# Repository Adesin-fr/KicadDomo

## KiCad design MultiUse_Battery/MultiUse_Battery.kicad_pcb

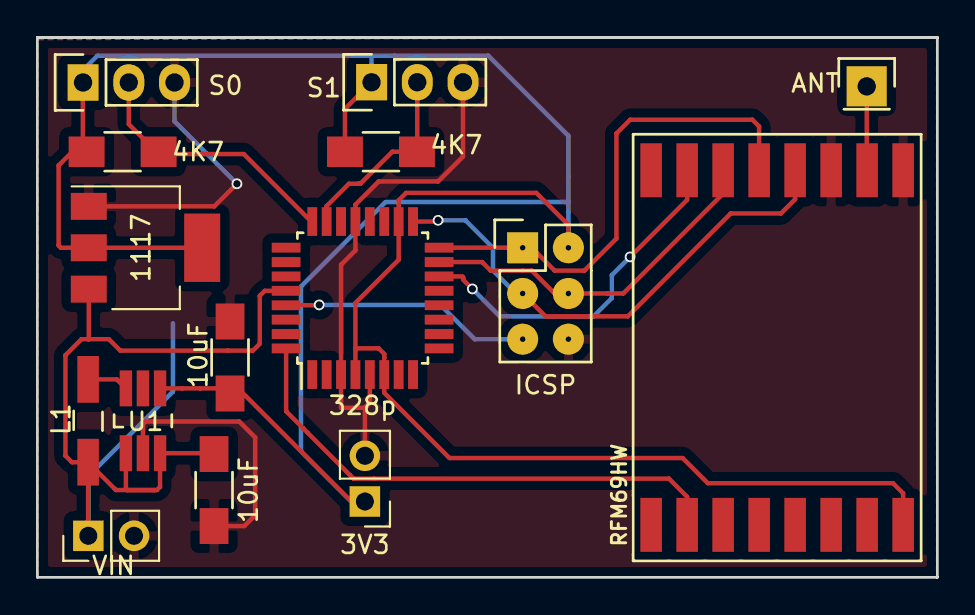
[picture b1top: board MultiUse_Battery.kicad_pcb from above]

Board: 2 copper layers, 50.0 x 30.0 mm, 16 parts (1 on the bottom side), 13 nets.

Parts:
3V3: CONN_01X02; Pin_Header_Straight_1x02_Pitch2.54mm
3V3#2: CR2032; BU2032_smd
4K7, 4K7#2: 4K7; R_1206_HandSoldering
10uF, 10uF#2: C; C_1206_HandSoldering
328p: ATMEGA328P-AU; TQFP-32_7x7mm_Pitch0.8mm
1117: AP111733; SOT-223
ANT: CONN_01X01; Pin_Header_Straight_1x01
ICSP: CONN_02X03; Pin_Header_Straight_2x03
L1: L; Choke_SMD_1206_Handsoldering
RFM69HW: RFM69HW; RFM69HW_SMD_Handsoldering
S0, S1: CONN_01X03; Pin_Header_Straight_1x03
U1: MAX1724; TSOT-6-MK06A_Handsoldering
VIN: CONN_01X02; Pin_Header_Straight_1x02_Pitch2.54mm

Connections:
/3V3: 3V3.1, 4K7.1, 4K7#2.1, 10uF#2.1, 328p.4, 328p.6, 328p.18, 1117.2, 1117.4, ICSP.2, RFM69HW.8, S0.1, S1.1, U1.4
/CSN: 328p.14, RFM69HW.15
/GND: 3V3.2, 3V3#2.2, 10uF.2, 10uF#2.2, 328p.3, 328p.5, 328p.21, 1117.1, ICSP.6, RFM69HW.9, RFM69HW.11, S0.3, S1.3, U1.2, VIN.2
/IRQ: 328p.32, RFM69HW.2
/MISO: 328p.16, ICSP.1, RFM69HW.13
/MOSI: 328p.15, ICSP.4, RFM69HW.14
/PC0: 4K7.2, 328p.24, S0.2
/PC1: 4K7#2.2, 328p.23, S1.2
/RST: 328p.29, ICSP.5
/SCK: 328p.17, ICSP.3, RFM69HW.12
/VIN: 3V3#2.1, 10uF.1, 328p.28, 1117.3, L1.1, U1.1, U1.3, VIN.1
unnamed: L1.2, U1.6
unnamed: ANT.1, RFM69HW.10

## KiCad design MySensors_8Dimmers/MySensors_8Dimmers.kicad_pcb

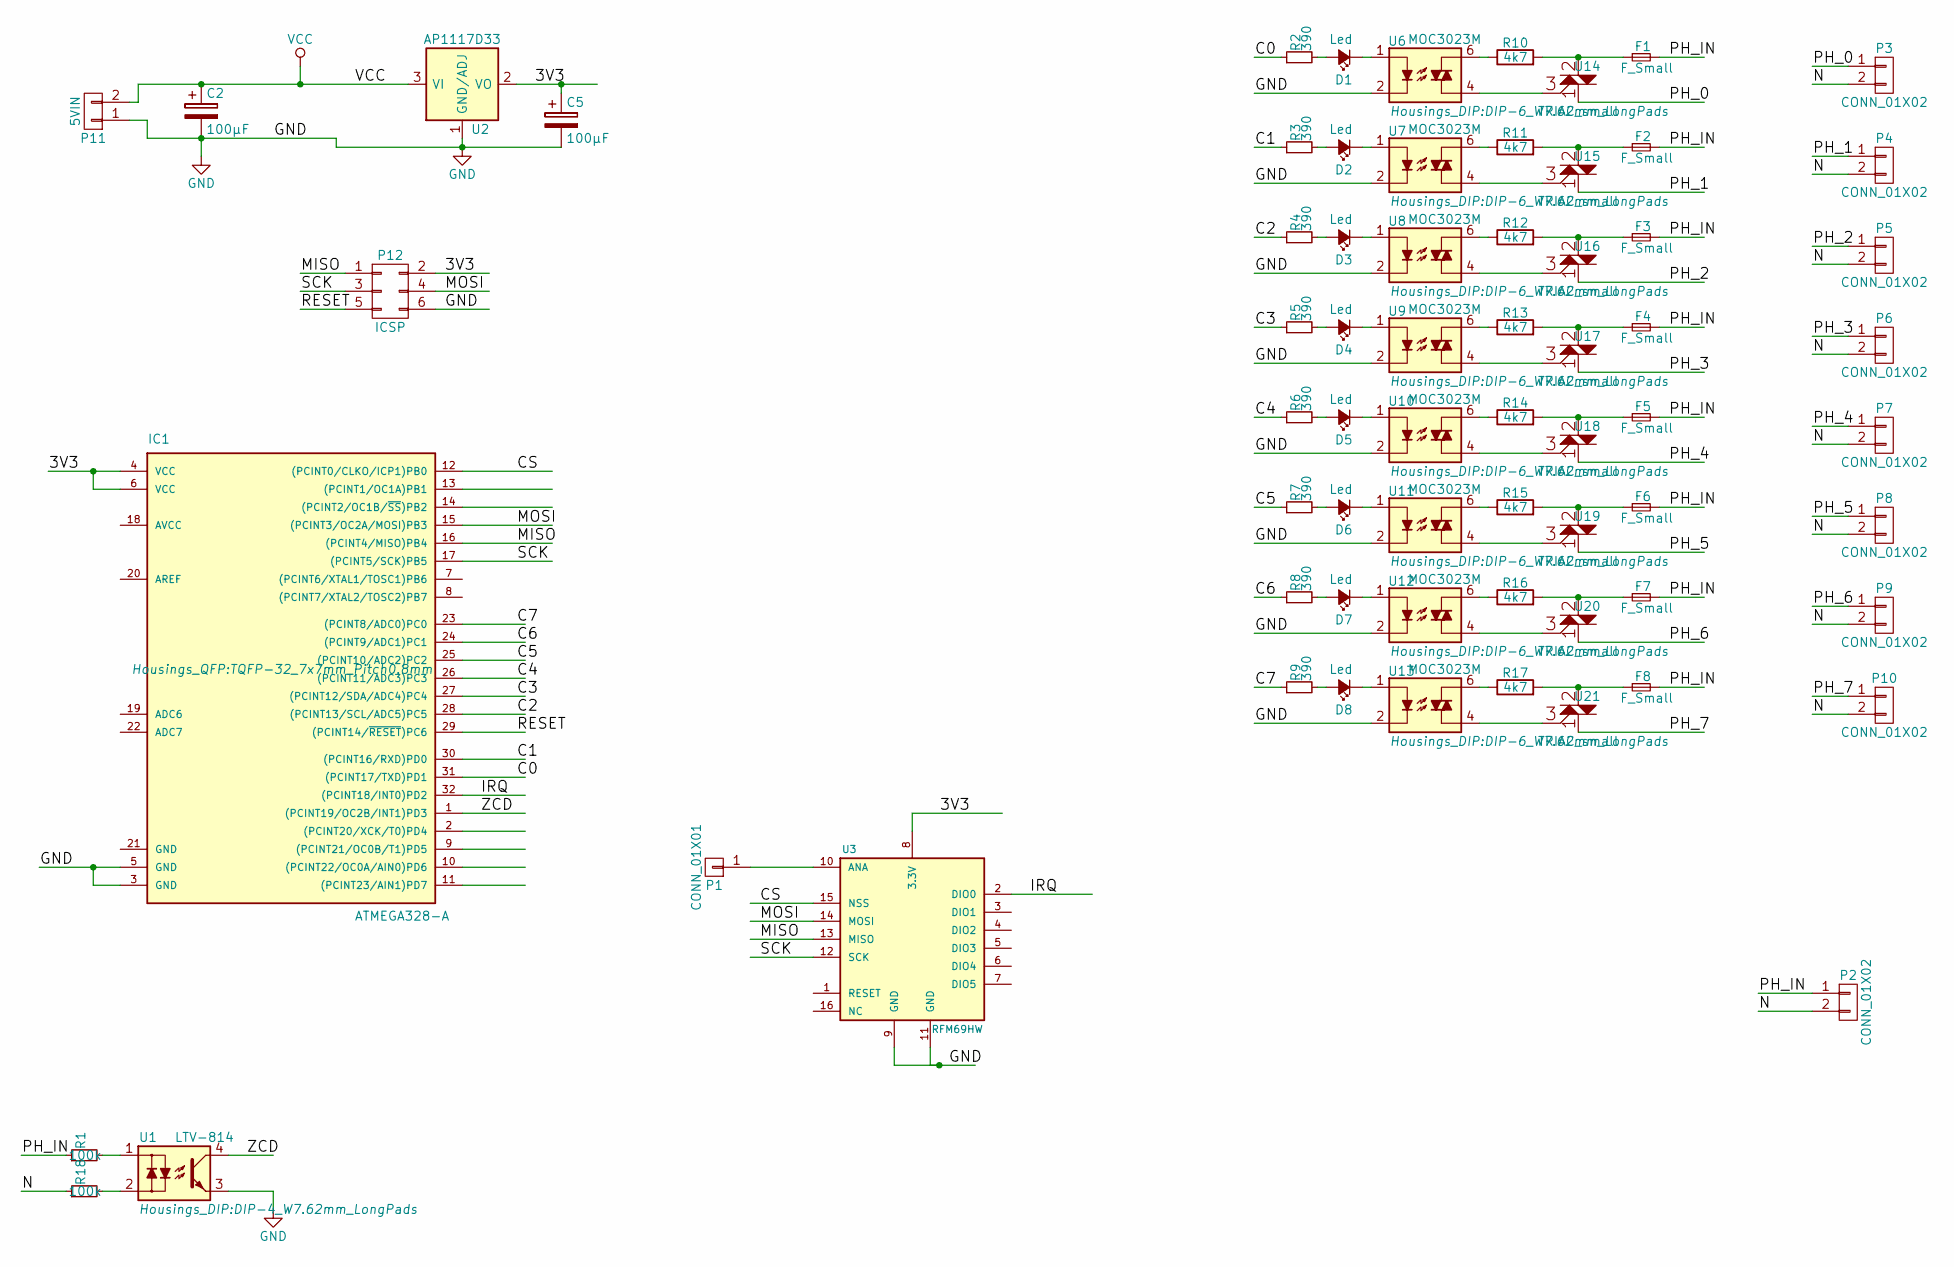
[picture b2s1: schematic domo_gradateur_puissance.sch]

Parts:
C2, C5: 100µF; C_Radial_D6.3_L11.2_P2.5
D1, D2, D3, D4, D5, D6, D7, D8: Led; LED-3MM
F1, F2, F3, F4, F5, F6, F7, F8: F_Small; Fuseholder5x20
IC1: ATMEGA328-A; TQFP-32_7x7mm_Pitch0.8mm
P1: CONN_01X01; Pin_Header_Straight_1x01_Pitch2.54mm
P2, P3, P4, P5, P6, P7, P8, P9, P10: CONN_01X02; bornier2
P11: 5VIN; bornier2
P12: ICSP; Pin_Header_Straight_2x03_Pitch2.54mm
R1, R18: 100k; RES35
R2, R3, R4, R5, R6, R7, R8, R9: 390; R_1206_HandSoldering
R10, R11, R12, R13, R14, R15, R16, R17: 4k7; RES35
U1: LTV-814; DIP-4_W7.62mm_LongPads
U2: AP1117D33; SOT-223
U3: RFM69HW; RFM69HW_SMD_Handsoldering
U6, U7, U8, U9, U10, U11, U12, U13: MOC3023M; DIP-6_W7.62mm_LongPads
U14, U15, U16, U17, U18, U19, U20, U21: TRIAC_small; TO-220

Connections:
/3V3: C5.1, IC1.4 (VCC), IC1.6 (VCC), P12.2, U2.2 (VO), U3.8 (3.3V); also elsewhere on the board
/C0: IC1.31 ((PCINT17/TXD)PD1), R2.1; also elsewhere on the board
/C1: IC1.30 ((PCINT16/RXD)PD0), R3.1; also elsewhere on the board
/C2: IC1.28 ((PCINT13/SCL/ADC5)PC5), R4.1; also elsewhere on the board
/C3: IC1.27 ((PCINT12/SDA/ADC4)PC4), R5.1; also elsewhere on the board
/C4: IC1.26 ((PCINT11/ADC3)PC3), R6.1; also elsewhere on the board
/C5: IC1.25 ((PCINT10/ADC2)PC2), R7.1; also elsewhere on the board
/C6: IC1.24 ((PCINT9/ADC1)PC1), R8.1; also elsewhere on the board
/C7: IC1.23 ((PCINT8/ADC0)PC0), R9.1; also elsewhere on the board
/N: P2.2, P3.2, P4.2, P5.2, P6.2, P7.2, P8.2, P9.2, P10.2, R18.1
/PH_0: P3.1, U14.1
/PH_1: P4.1, U15.1
/PH_2: P5.1, U16.1
/PH_3: P6.1, U17.1
/PH_4: P7.1, U18.1
/PH_5: P8.1, U19.1
/PH_6: P9.1, U20.1
/PH_7: P10.1, U21.1
/PH_IN: F1.2, F2.2, F3.2, F4.2, F5.2, F6.2, F7.2, F8.2, P2.1, R1.1
/ZCD: IC1.1 ((PCINT19/OC2B/INT1)PD3), U1.4; also elsewhere on the board
GND: C2.2, C5.2, IC1.3 (GND), IC1.5 (GND), P11.1, P12.6, U1.3, U2.1 (GND/ADJ), U3.9 (GND), U3.11 (GND), U6.2, U7.2, U8.2, U9.2, U10.2, U11.2, U12.2, U13.2; also elsewhere on the board
unnamed: D1.1 (K), U6.1
unnamed: D1.2 (A), R2.2
unnamed: D2.1 (K), U7.1
unnamed: D2.2 (A), R3.2
unnamed: D3.1 (K), U8.1
unnamed: D3.2 (A), R4.2
unnamed: D4.1 (K), U9.1
unnamed: D4.2 (A), R5.2
unnamed: D5.1 (K), U10.1
unnamed: D5.2 (A), R6.2
unnamed: D6.1 (K), U11.1
unnamed: D6.2 (A), R7.2
unnamed: D7.1 (K), U12.1
unnamed: D7.2 (A), R8.2
unnamed: D8.1 (K), U13.1
unnamed: D8.2 (A), R9.2
unnamed: F1.1, R10.2, U14.2
unnamed: F2.1, R11.2, U15.2
unnamed: F3.1, R12.2, U16.2
unnamed: F4.1, R13.2, U17.2
unnamed: F5.1, R14.2, U18.2
unnamed: F6.1, R15.2, U19.2
unnamed: F7.1, R16.2, U20.2
unnamed: F8.1, R17.2, U21.2
unnamed: IC1.12 ((PCINT0/CLKO/ICP1)PB0), U3.15 (NSS)
unnamed: IC1.15 ((PCINT3/OC2A/MOSI)PB3), P12.4, U3.14 (MOSI)
unnamed: IC1.16 ((PCINT4/MISO)PB4), P12.1, U3.13 (MISO)
unnamed: IC1.17 ((PCINT5/SCK)PB5), P12.3, U3.12 (SCK)
unnamed: IC1.29 ((PCINT14/~RESET~)PC6), P12.5
unnamed: IC1.32 ((PCINT18/INT0)PD2), U3.2 (DIO0)
unnamed 69: P1.1, U3.10 (ANA); also elsewhere on the board
unnamed: R1.2, U1.1
unnamed: R10.1, U6.6
unnamed: R11.1, U7.6
unnamed: R12.1, U8.6
unnamed: R13.1, U9.6
unnamed: R14.1, U10.6
unnamed: R15.1, U11.6
unnamed: R16.1, U12.6
unnamed: R17.1, U13.6
unnamed: R18.2, U1.2
unnamed: U10.4, U18.3
unnamed: U11.4, U19.3
unnamed: U12.4, U20.3
unnamed: U13.4, U21.3
unnamed: U6.4, U14.3
unnamed: U7.4, U15.3
unnamed: U8.4, U16.3
unnamed: U9.4, U17.3
VCC: C2.1, P11.2, U2.3 (VI); also elsewhere on the board

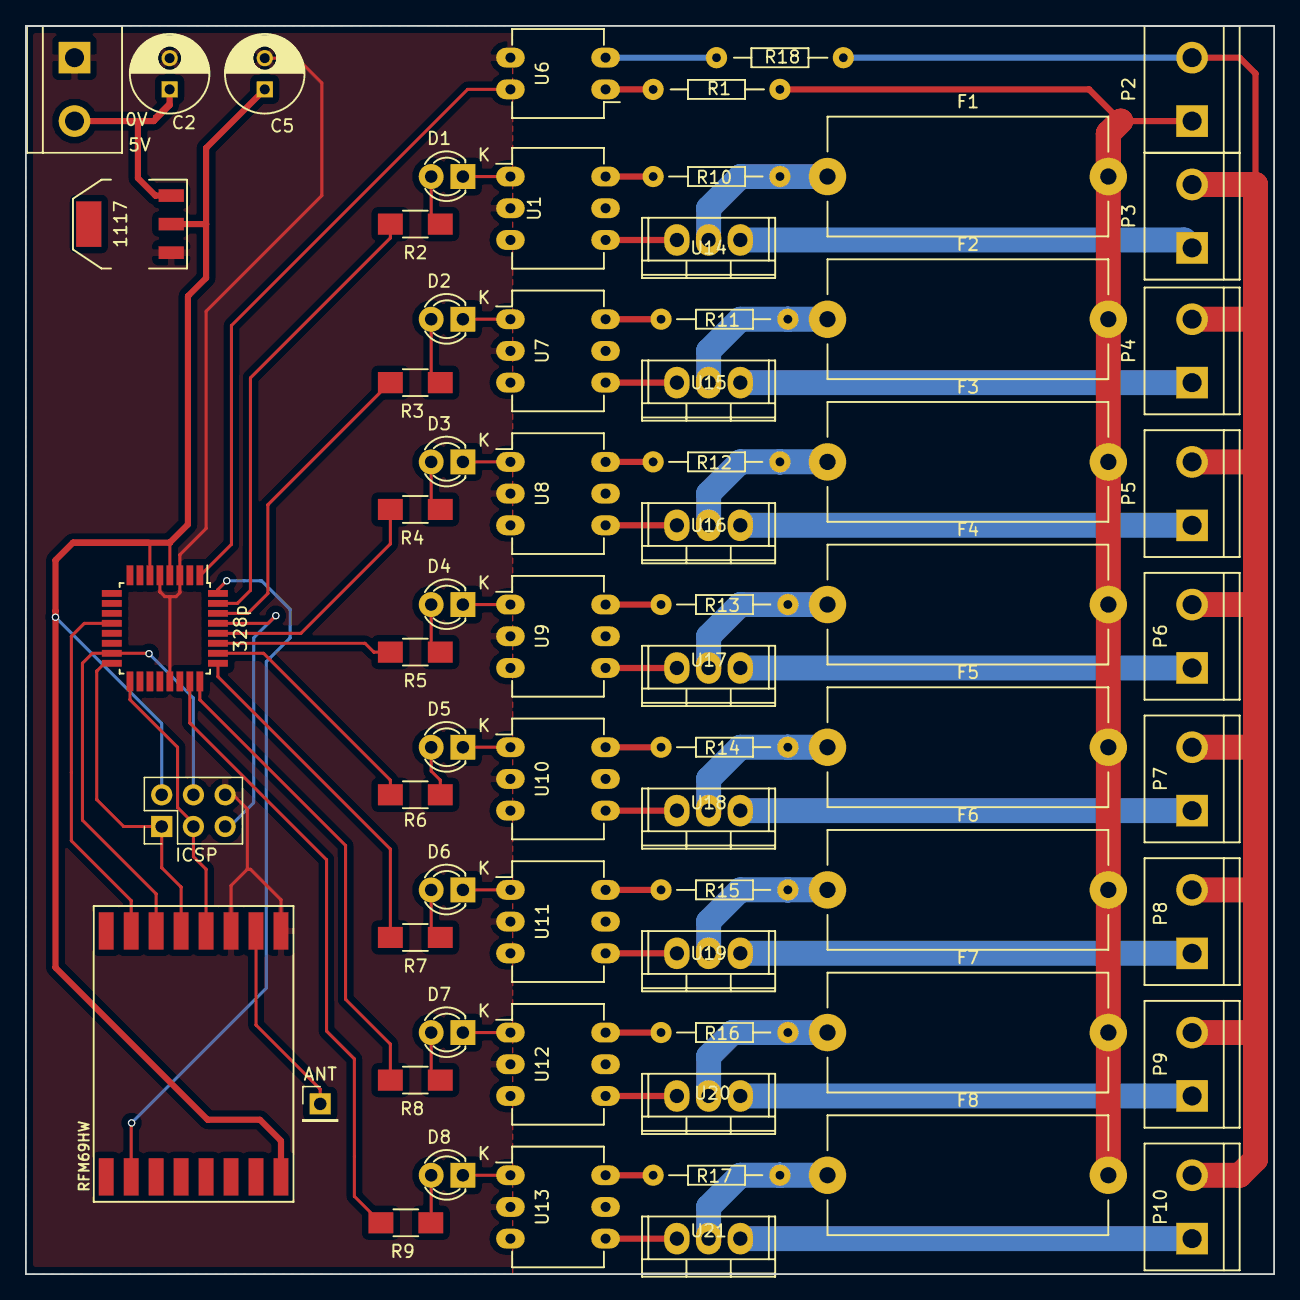
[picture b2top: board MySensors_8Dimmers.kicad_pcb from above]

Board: 2 copper layers, 100.0 x 100.0 mm, 68 parts (0 on the bottom side), 71 nets.

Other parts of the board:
5V: 5VIN; bornier2
328p: ATMEGA328-A; TQFP-32_7x7mm_Pitch0.8mm
1117: AP1117D33; SOT-223
ANT: CONN_01X01; Pin_Header_Straight_1x01_Pitch2.54mm
ICSP: ICSP; Pin_Header_Straight_2x03_Pitch2.54mm
RFM69HW: RFM69HW; RFM69HW_SMD_Handsoldering

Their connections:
/3V3: 328p.4, 328p.6, 1117.2, ICSP.2, RFM69HW.8; also elsewhere on the board
/C0: 328p.31; also elsewhere on the board
/C1: 328p.30; also elsewhere on the board
/C2: 328p.28; also elsewhere on the board
/C3: 328p.27; also elsewhere on the board
/C4: 328p.26; also elsewhere on the board
/C5: 328p.25; also elsewhere on the board
/C6: 328p.24; also elsewhere on the board
/C7: 328p.23; also elsewhere on the board
/CS: 328p.12, RFM69HW.15
/IRQ: 328p.32, RFM69HW.2
/MISO: 328p.16, ICSP.1, RFM69HW.13
/MOSI: 328p.15, ICSP.4, RFM69HW.14
/RESET: 328p.29, ICSP.5
/SCK: 328p.17, ICSP.3, RFM69HW.12
/ZCD: 328p.1; also elsewhere on the board
GND: 5V.1, 328p.3, 328p.5, 328p.21, 1117.1, ICSP.6, RFM69HW.9, RFM69HW.11; also elsewhere on the board
unnamed 69: ANT.1, RFM69HW.10; also elsewhere on the board
VCC: 5V.2, 1117.3; also elsewhere on the board

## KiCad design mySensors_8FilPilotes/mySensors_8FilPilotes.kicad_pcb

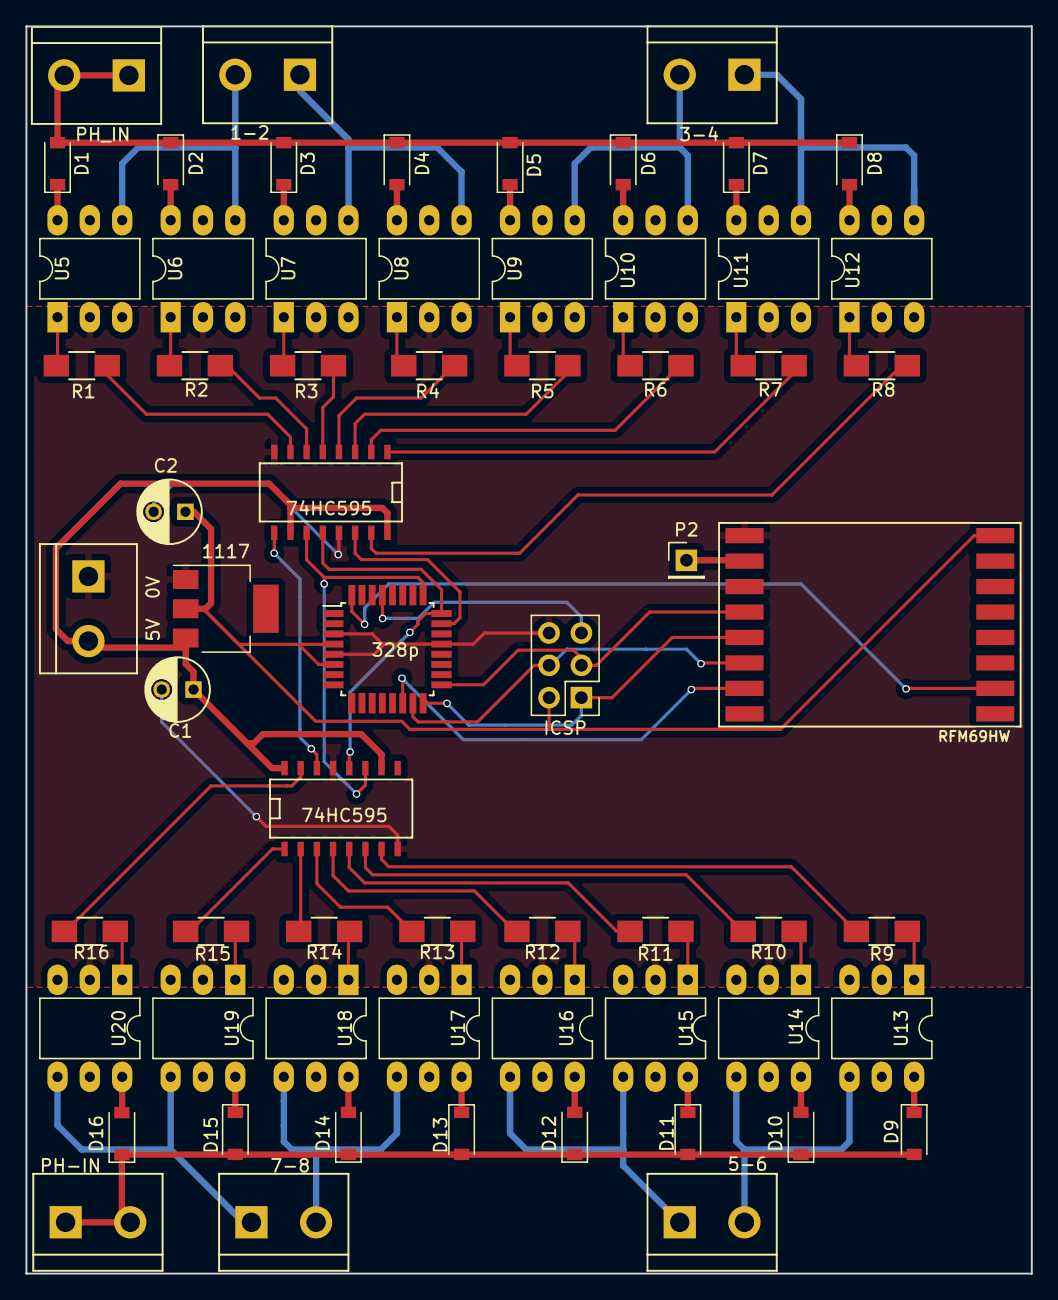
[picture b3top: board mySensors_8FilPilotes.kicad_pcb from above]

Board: 2 copper layers, 79.0 x 98.0 mm, 64 parts (0 on the bottom side), 71 nets.

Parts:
1-2, 3-4, 5-6, 7-8: CONN_01X02; bornier2
5V  0V: 5VIN; bornier2
74HC595, 74HC595#2: 74HC595; SO-16-N
328p: ATMEGA328-A; TQFP-32_7x7mm_Pitch0.8mm
1117: AMS1117; SOT-223
C1, C2: 10uF; C_Radial_D5_L6_P2.5
D1, D2, D3, D4, D5, D6, D7, D8, D9, D10, D11, D12, D13, D14, D15, D16: D; SOD-123
ICSP: CONN_02X03; Pin_Header_Straight_2x03_Pitch2.54mm
P2: ANT; Pin_Header_Straight_1x01_Pitch2.54mm
PH-IN: CONN_01X02; bornier2
PH_IN: CONN_01X02; bornier2
R1, R2, R3, R4, R5, R6, R7, R8, R9, R10, R11, R12, R13, R14, R15, R16: R; R_1206_HandSoldering
RFM69HW: RFM69HW; RFM69HW_SMD_Handsoldering
U5, U6, U7, U8, U9, U10, U11, U12, U13, U14, U15, U16, U17, U18, U19, U20: MOC3041M; DIP-6_W7.62mm_LongPads

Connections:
/3V3: 328p.4, 328p.6, 1117.2, C2.1, ICSP.2, RFM69HW.8
/CS: 328p.14, RFM69HW.15
/FP1: 1-2.2, U5.4, U6.4
/FP1_A: 74HC595.7, R1.2
/FP1_B: 74HC595.6, R2.2
/FP2: 1-2.1, U7.4, U8.4
/FP2_A: 74HC595.5, R3.2
/FP2_B: 74HC595.4, R4.2
/FP3: 3-4.2, U9.4, U10.4
/FP3_A: 74HC595.3, R5.2
/FP3_B: 74HC595.2, R6.2
/FP4: 3-4.1, U11.4, U12.4
/FP4_A: 74HC595.1, R7.2
/FP4_B: 74HC595.15, R8.2
/FP5: 5-6.2, U13.4, U14.4
/FP5_A: 74HC595#2.7, R9.2
/FP5_B: 74HC595#2.6, R10.2
/FP6: 5-6.1, U15.4, U16.4
/FP6_A: 74HC595#2.5, R11.2
/FP6_B: 74HC595#2.4, R12.2
/FP7: 7-8.2, U17.4, U18.4
/FP7_A: 74HC595#2.3, R13.2
/FP7_B: 74HC595#2.2, R14.2
/FP8: 7-8.1, U19.4, U20.4
/FP8_A: 74HC595#2.1, R15.2
/FP8_B: 74HC595#2.15, R16.2
/IRQ: 328p.32, RFM69HW.2
/MISO: 328p.16, ICSP.1, RFM69HW.13
/MOSI: 328p.15, ICSP.4, RFM69HW.14
/PH_IN: D1.2, D2.1, D3.2, D4.1, D5.2, D6.1, D7.2, D8.1, D9.2, D10.1, D11.2, D12.1, D13.2, D14.1, D15.2, D16.1, PH-IN.1, PH-IN.2, PH_IN.1, PH_IN.2
/RCLK: 74HC595.12, 74HC595#2.12, 328p.24
/RESET: 328p.29, ICSP.5
/SCK: 328p.17, ICSP.3, RFM69HW.12
/SER: 74HC595.14, 328p.23
/SER2: 74HC595.9, 74HC595#2.14
/SRCLK: 74HC595.11, 74HC595#2.11, 328p.25
GND: 5V 0V.1, 74HC595.8, 74HC595.13, 74HC595#2.8, 74HC595#2.13, 328p.3, 328p.5, 328p.21, 1117.1, C1.2, C2.2, ICSP.6, RFM69HW.9, RFM69HW.11, U5.2, U6.2, U7.2, U8.2, U9.2, U10.2, U11.2, U12.2, U13.2, U14.2, U15.2, U16.2, U17.2, U18.2, U19.2, U20.2
unnamed: D1.1, U5.6
unnamed: D2.2, U6.6
unnamed: D3.1, U7.6
unnamed: D4.2, U8.6
unnamed: D5.1, U9.6
unnamed: D6.2, U10.6
unnamed: D7.1, U11.6
unnamed: D8.2, U12.6
unnamed: D9.1, U13.6
unnamed: D10.2, U14.6
unnamed: D11.1, U15.6
unnamed: D12.2, U16.6
unnamed: D13.1, U17.6
unnamed: D14.2, U18.6
unnamed: D15.1, U19.6
unnamed: D16.2, U20.6
unnamed: P2.1, RFM69HW.10
unnamed: R1.1, U5.1
unnamed: R2.1, U6.1
unnamed: R3.1, U7.1
unnamed: R4.1, U8.1
unnamed: R5.1, U9.1
unnamed: R6.1, U10.1
unnamed: R7.1, U11.1
unnamed: R8.1, U12.1
unnamed: R9.1, U13.1
unnamed: R10.1, U14.1
unnamed: R11.1, U15.1
unnamed: R12.1, U16.1
unnamed: R13.1, U17.1
unnamed: R14.1, U18.1
unnamed: R15.1, U19.1
unnamed: R16.1, U20.1
VCC: 5V 0V.2, 74HC595.10, 74HC595.16, 74HC595#2.10, 74HC595#2.16, 1117.3, C1.1

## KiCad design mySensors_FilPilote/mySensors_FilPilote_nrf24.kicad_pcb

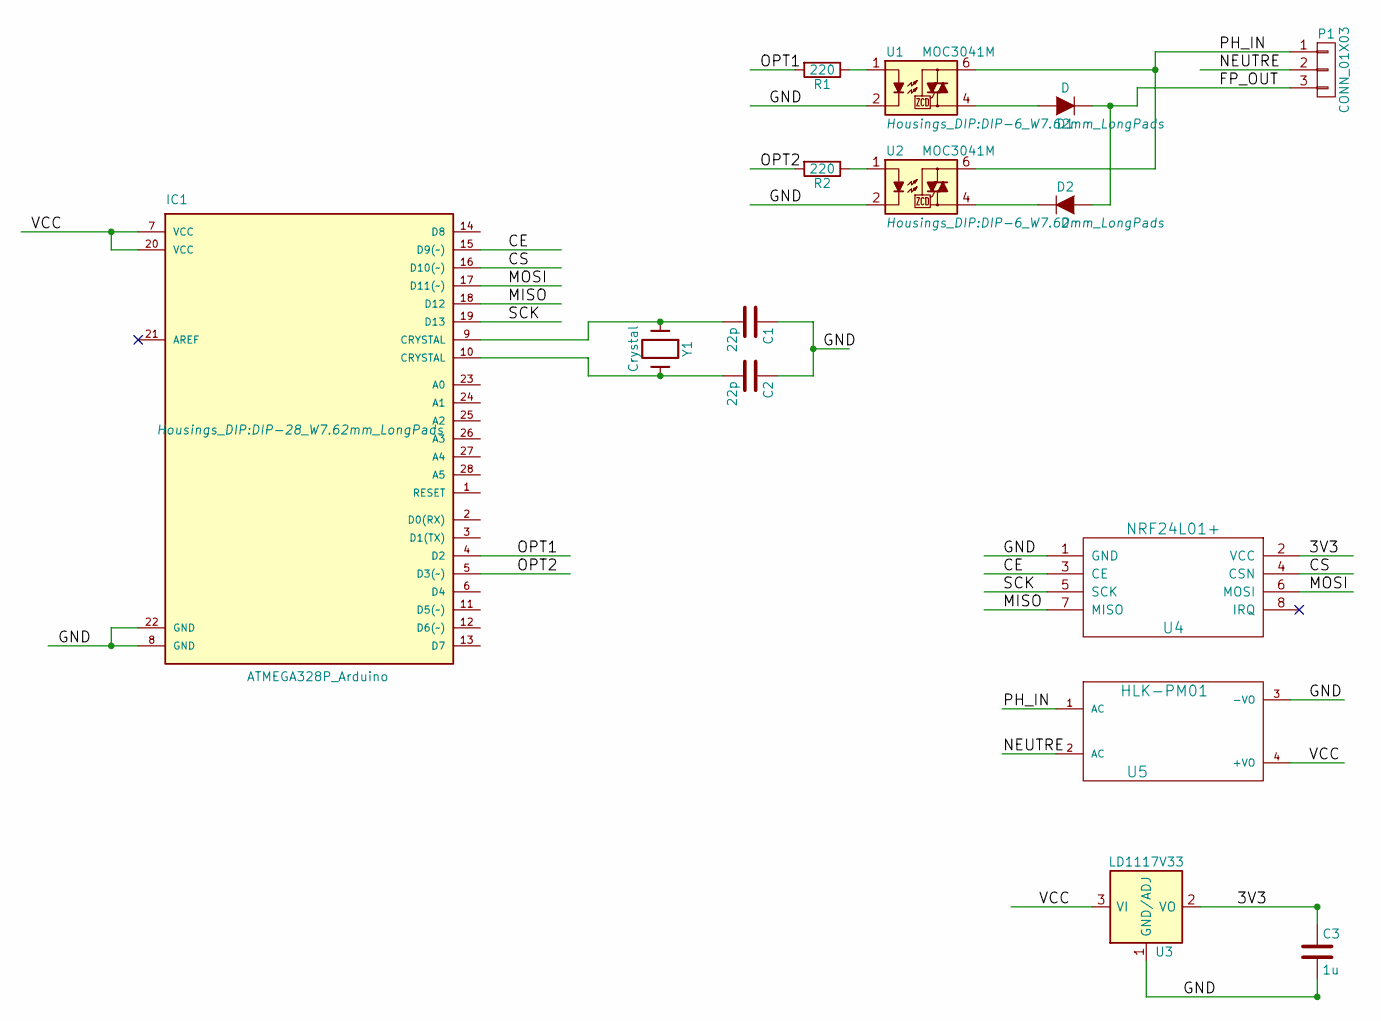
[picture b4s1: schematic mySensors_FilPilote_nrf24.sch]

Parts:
C1, C2: 22p; C_Disc_D3_P2.5
C3: 1u; C_Radial_D5_L11_P2
D1, D2: D; Diode_DO-41_SOD81_Horizontal_RM10
IC1: ATMEGA328P_Arduino; DIP-28_W7.62mm_LongPads
P1: CONN_01X03; bornier3
R1, R2: 220; RES35
U1, U2: MOC3041M; DIP-6_W7.62mm_LongPads
U3: LD1117V33; Diode_TO-220_Dual_CommonCathode_Vertical
U4: NRF24L01+; NRF24L01
U5: HLK-PM01
Y1: Crystal; Crystal_HC49-U_Vertical

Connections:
/3V3: C3.1, U3.2 (VO), U4.2 (VCC)
/CE: IC1.15 (D9(~~)), U4.3 (CE)
/CS: IC1.16 (D10(~~)), U4.4 (CSN)
/FP_OUT: D1.1 (K), D2.2 (A), P1.3
/GND: C1.1, C2.1, C3.2, IC1.8 (GND), IC1.22 (GND), U1.2, U2.2, U3.1 (GND/ADJ), U4.1 (GND), U5.3 (-VO)
/MISO: IC1.18 (D12), U4.7 (MISO)
/MOSI: IC1.17 (D11(~~)), U4.6 (MOSI)
/NEUTRE: P1.2, U5.2 (AC)
/OPT1: IC1.4 (D2), R1.2
/OPT2: IC1.5 (D3(~~)), R2.2
/PH_IN: P1.1, U1.6, U2.6, U5.1 (AC)
/SCK: IC1.19 (D13), U4.5 (SCK)
/VCC: IC1.7 (VCC), IC1.20 (VCC), U3.3 (VI), U5.4 (+VO)
unnamed: C1.2, IC1.9 (CRYSTAL), Y1.1
unnamed: C2.2, IC1.10 (CRYSTAL), Y1.2
unnamed: D1.2 (A), U1.4
unnamed: D2.1 (K), U2.4
unnamed: R1.1, U1.1
unnamed: R2.1, U2.1

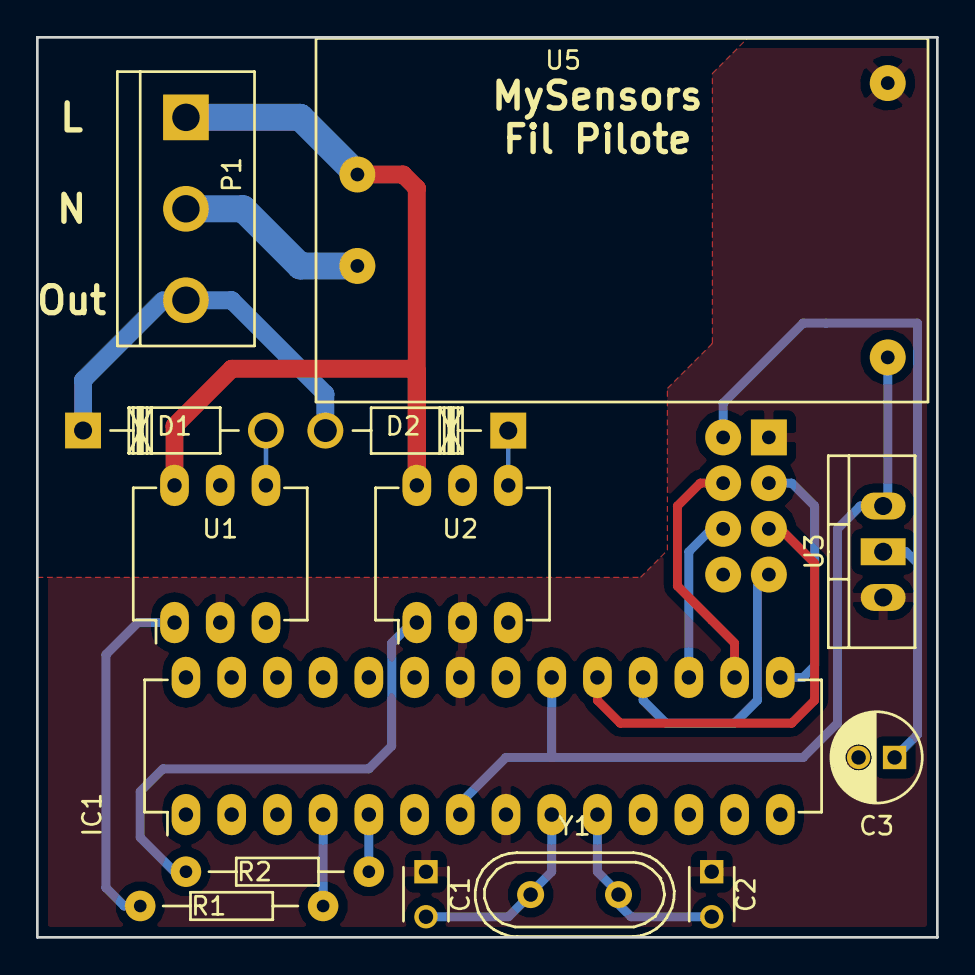
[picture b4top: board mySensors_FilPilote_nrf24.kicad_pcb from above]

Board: 2 copper layers, 50.0 x 50.0 mm, 15 parts (1 on the bottom side), 19 nets.

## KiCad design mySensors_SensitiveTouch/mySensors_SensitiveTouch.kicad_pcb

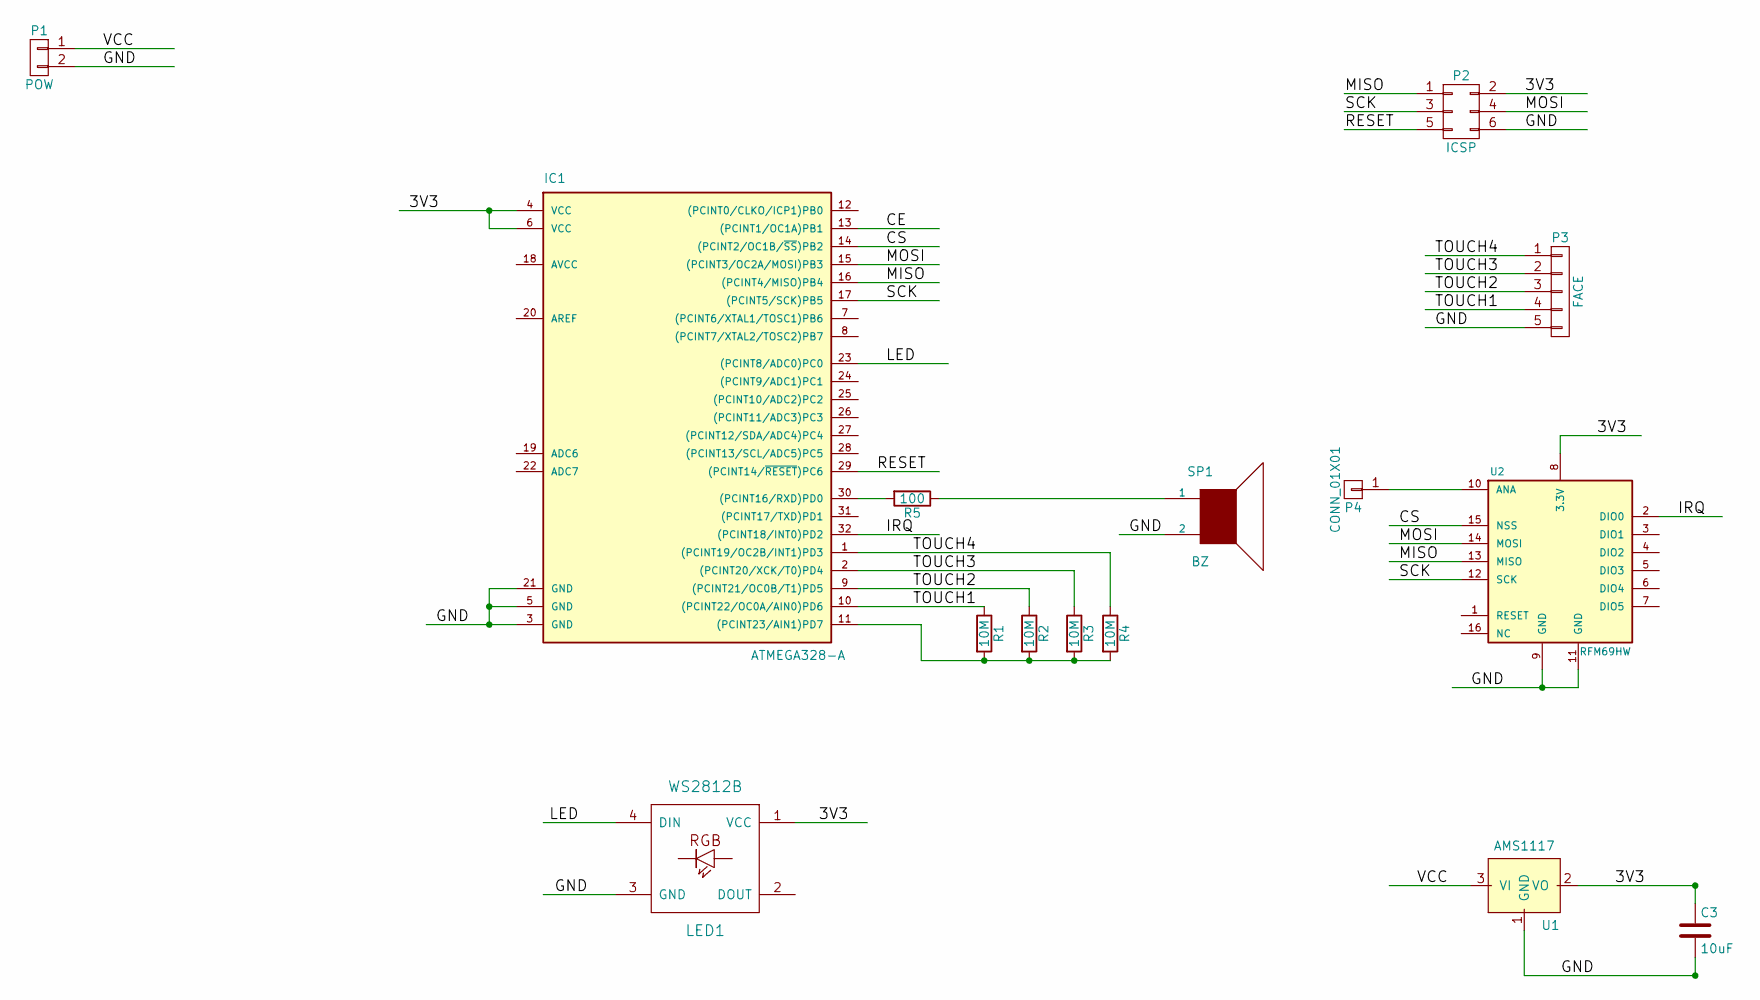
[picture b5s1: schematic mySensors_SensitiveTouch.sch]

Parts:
C3: 10uF; C_1206_HandSoldering
IC1: ATMEGA328-A; TQFP-32_7x7mm_Pitch0.8mm
LED1: WS2812B; LED_WS2812B-PLCC4
P1: POW; bornier2
P2: ICSP; Pin_Header_Straight_1x06_Pitch2.54mm
P3: FACE; Pin_Header_Straight_1x05_Pitch2.54mm
P4: CONN_01X01; Pin_Header_Straight_1x01_Pitch2.54mm
R1, R2, R3, R4: 10M; R_1206_HandSoldering
R5: 100; R_1206_HandSoldering
SP1: BZ; Buzzer_12x9.5RM7.6
U1: AMS1117; SOT-223
U2: RFM69HW; RFM69HW_SMD_Handsoldering

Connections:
/3V3: C3.1, IC1.4 (VCC), IC1.6 (VCC), LED1.1 (VCC), P2.2, U1.2 (VO), U2.8 (3.3V)
/CE: IC1.13 ((PCINT1/OC1A)PB1)
/CS: IC1.14 ((PCINT2/OC1B/~SS~)PB2), U2.15 (NSS)
/GND: C3.2, IC1.3 (GND), IC1.5 (GND), IC1.21 (GND), LED1.3 (GND), P1.2, P2.6, P3.5, SP1.2, U1.1 (GND), U2.9 (GND), U2.11 (GND)
/IRQ: IC1.32 ((PCINT18/INT0)PD2), U2.2 (DIO0)
/LED: IC1.23 ((PCINT8/ADC0)PC0), LED1.4 (DIN)
/MISO: IC1.16 ((PCINT4/MISO)PB4), P2.1, U2.13 (MISO)
/MOSI: IC1.15 ((PCINT3/OC2A/MOSI)PB3), P2.4, U2.14 (MOSI)
/RESET: IC1.29 ((PCINT14/~RESET~)PC6), P2.5
/SCK: IC1.17 ((PCINT5/SCK)PB5), P2.3, U2.12 (SCK)
/TOUCH1: IC1.10 ((PCINT22/OC0A/AIN0)PD6), P3.4, R1.1
/TOUCH2: IC1.9 ((PCINT21/OC0B/T1)PD5), P3.3, R2.1
/TOUCH3: IC1.2 ((PCINT20/XCK/T0)PD4), P3.2, R3.1
/TOUCH4: IC1.1 ((PCINT19/OC2B/INT1)PD3), P3.1, R4.1
/VCC: P1.1, U1.3 (VI)
unnamed: IC1.11 ((PCINT23/AIN1)PD7), R1.2, R2.2, R3.2, R4.2
unnamed: IC1.30 ((PCINT16/RXD)PD0), R5.2
unnamed 31: P4.1, U2.10 (ANA); also elsewhere on the board
unnamed: R5.1, SP1.1

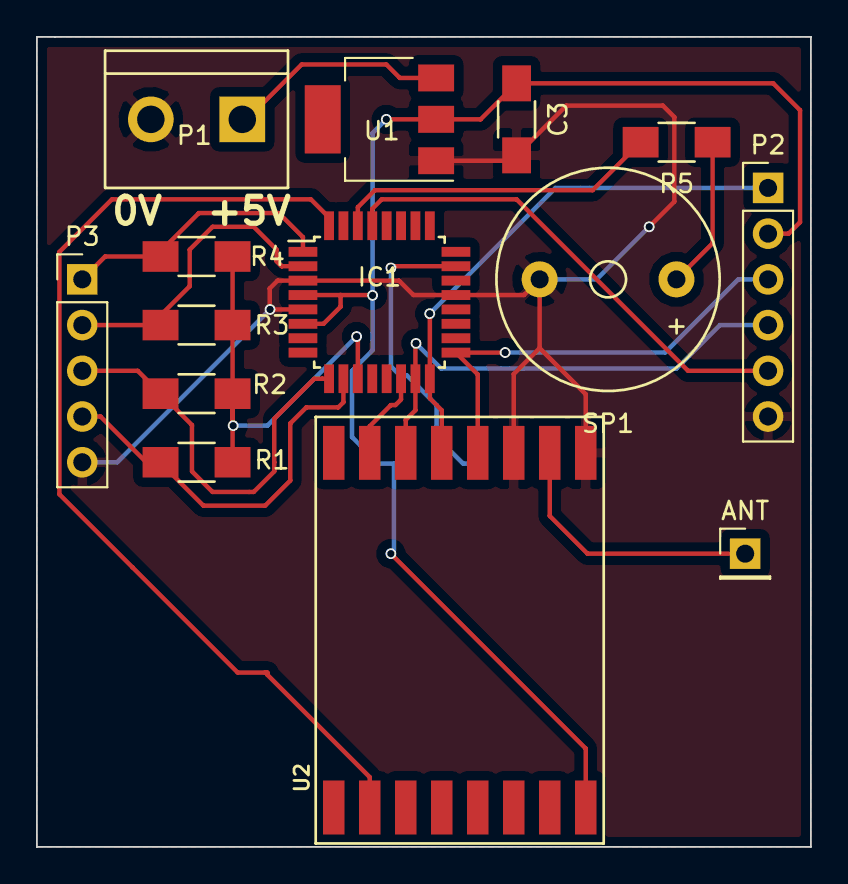
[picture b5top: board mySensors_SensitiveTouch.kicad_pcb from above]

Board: 2 copper layers, 43.0 x 45.0 mm, 15 parts (1 on the bottom side), 18 nets.

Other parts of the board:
ANT: ANT; Pin_Header_Straight_1x01_Pitch2.54mm

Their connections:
unnamed 31: ANT.1; also elsewhere on the board
